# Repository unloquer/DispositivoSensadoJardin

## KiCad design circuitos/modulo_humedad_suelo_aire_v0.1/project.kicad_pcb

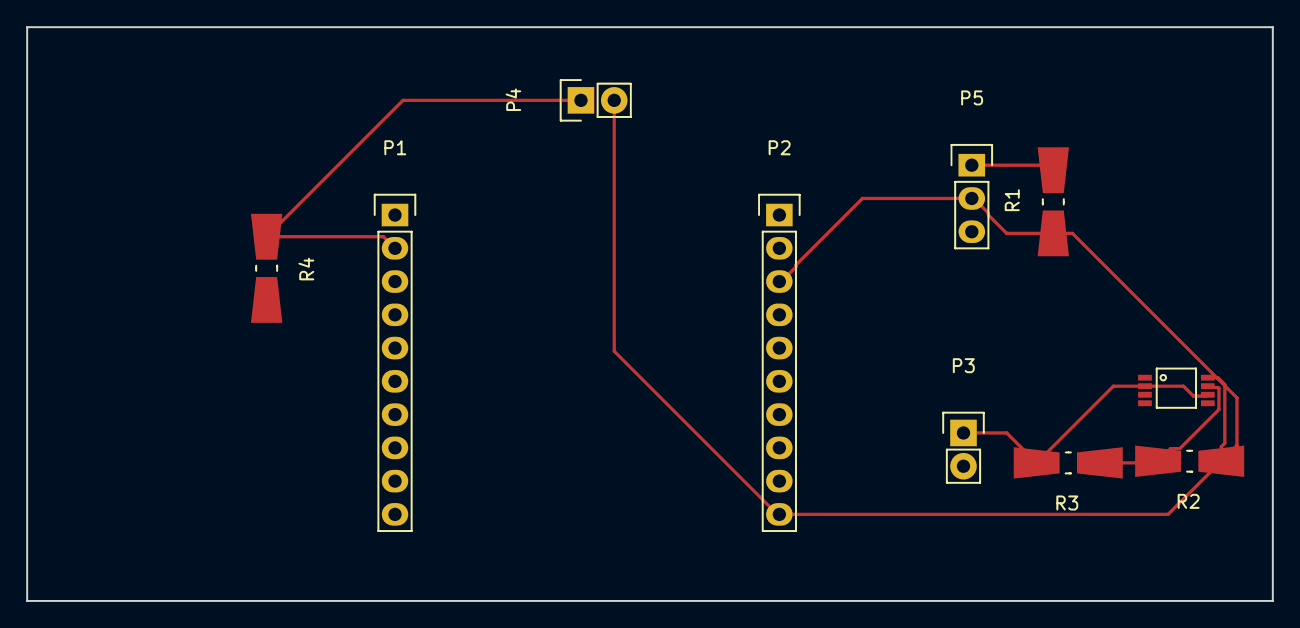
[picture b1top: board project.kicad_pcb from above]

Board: 2 copper layers, 95.1 x 43.8 mm, 10 parts (0 on the bottom side), 9 nets.

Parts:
P1: ESP_B; Pin_Header_Straight_1x10
P2: ESP_A; Pin_Header_Straight_1x10
P3: Humedad_suelo; Pin_Header_Straight_1x02
P4: Fotocelda; Pin_Header_Straight_1x02
P5: DHT11; Pin_Header_Straight_1x03
R1, R2, R3, R4: 10K; Resistor_SMDuniversal_0805to1206_HandSoldering
U2: 555

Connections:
+5V: P2.3, P2.10, P4.2, P5.2, R1.1, R2.1, U2.4, U2.8
/3.3V: P1.8, P2.8
/ADC: P1.2, P4.1, R4.1
/HUM_electrodeA: P3.1, R3.2, U2.2, U2.6
/gpio4: P2.4, U2.3
/gpio13: P1.7, P2.7
GND: P1.9, P2.9, P3.2, P5.3, R4.2, U2.1
unnamed: P5.1, R1.2
unnamed: R2.2, R3.1, U2.7

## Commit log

2016-05-14 Código básico que lee cantidad de luz mediante fotocelda, humedad en la tierra mediante la lectura de la frecuencia de una señal pulsada y temperatura y humedad desde un DHT11. Se conecta a una red w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
2016-05-14 agregado readme con foto
2016-05-14 agregado ntpClient, gitignore, makefile pio vim, timestamp no funciona
2016-05-20 solucionado problema con envio de la fecha al servidor
2016-06-29 poyecto kicad modulo humedad suelo, aire, luz
